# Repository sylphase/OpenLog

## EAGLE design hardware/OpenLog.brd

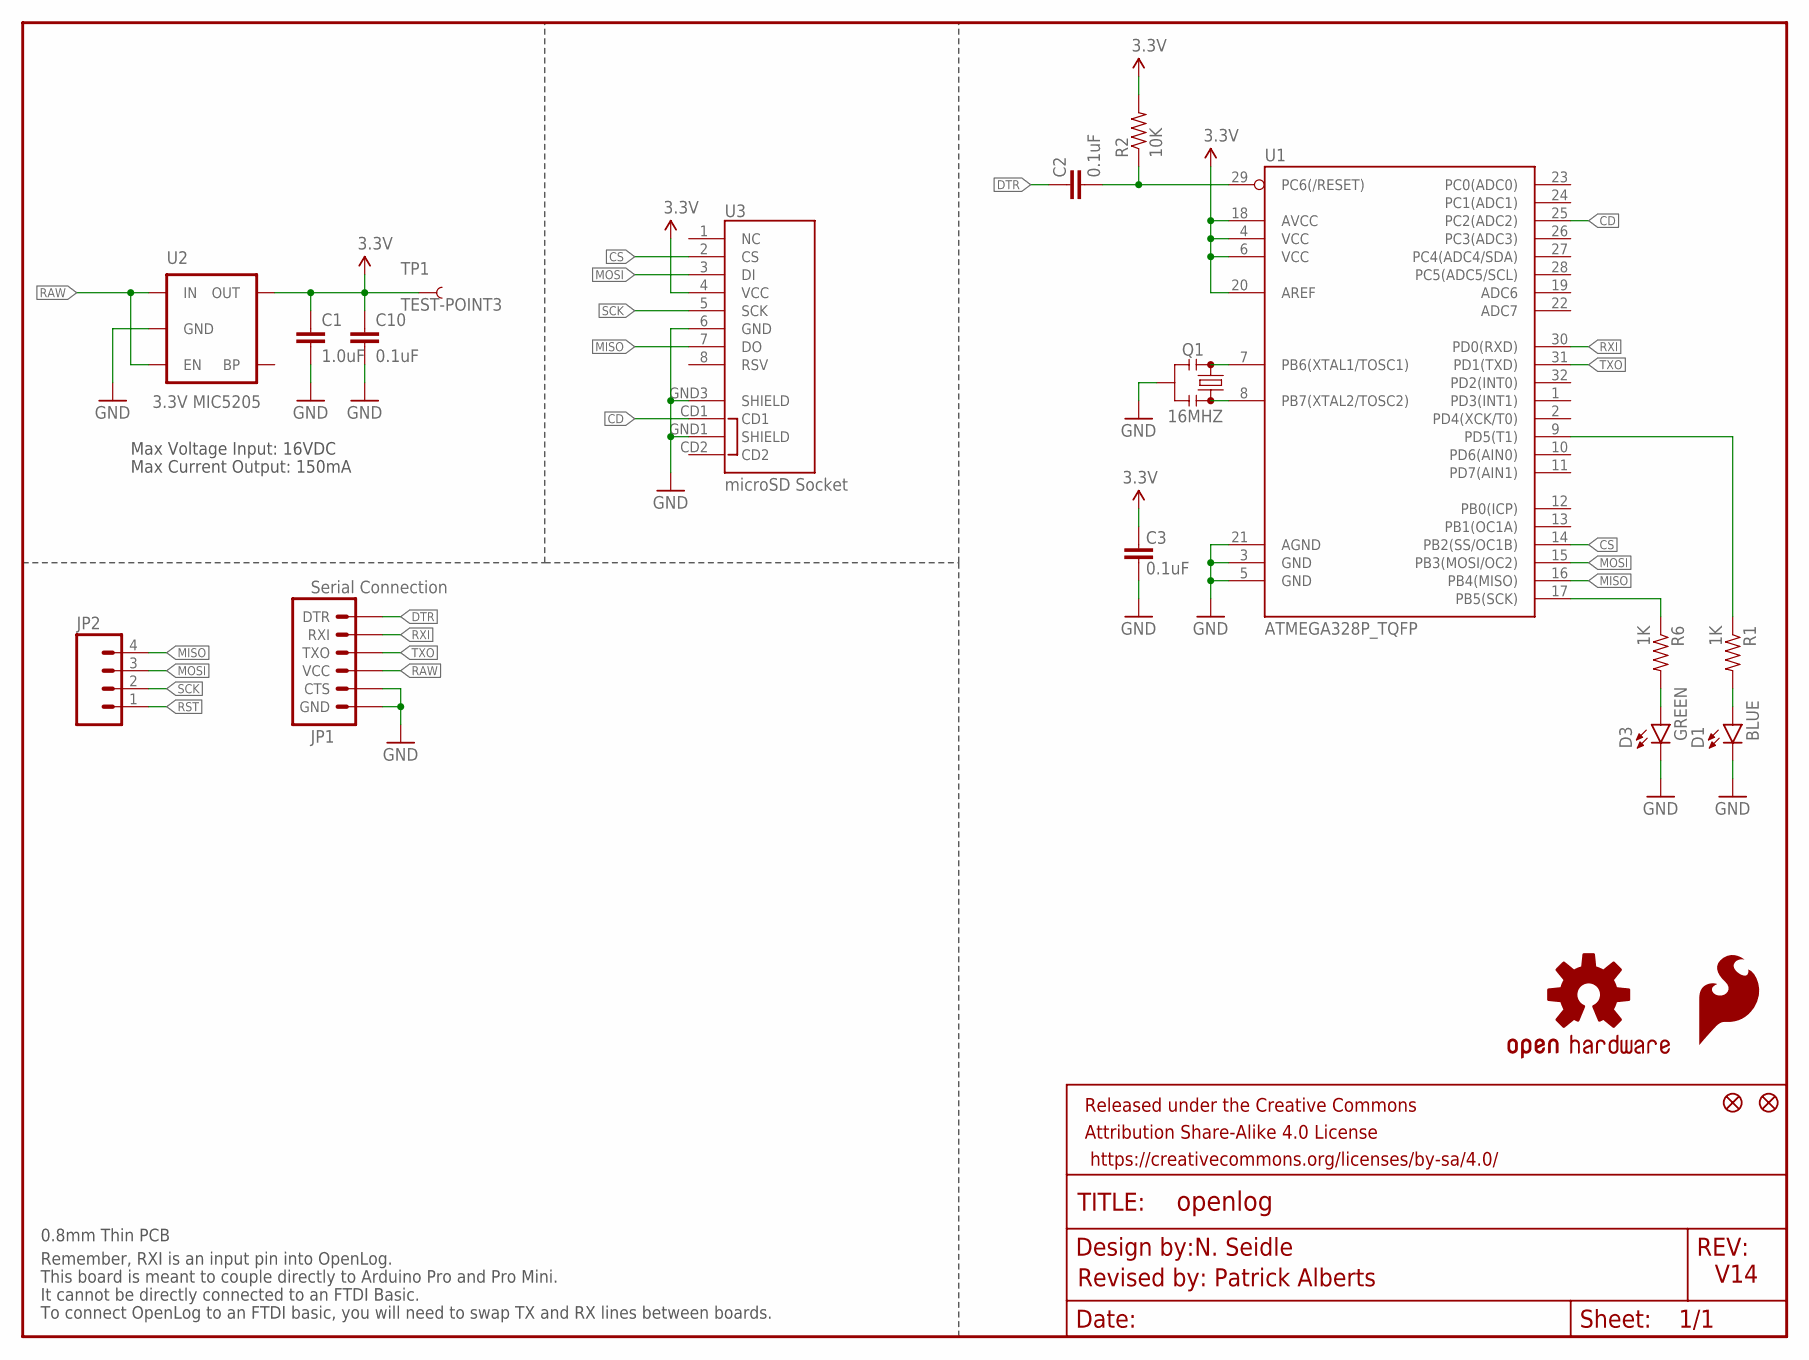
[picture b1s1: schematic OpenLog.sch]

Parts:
C1: 1.0uF; 0603-CAP
C2, C3, C10: 0.1uF; 0603-CAP
D1: BLUE; LED-0603
D3: GREEN; LED-0603
FID1, FID2: FIDUCIALUFIDUCIAL; MICRO-FIDUCIAL
FRAME1: FRAME-LETTER; CREATIVE_COMMONS
JP1: Serial Connection; 1X06
JP2: M04PTH; 1X04
LOGO1: SFE_LOGO_FLAME.1_INCH; SFE_LOGO_FLAME_.1
LOGO2: OSHW-LOGOS; OSHW-LOGO-S
Q1: 16MHZ; RESONATOR-SMD
R1, R6: 1K; 0603-RES
R2: 10K; 0603-RES
TP1: TEST-POINT3; PAD.03X.03
U1: ATMEGA328P_TQFP; TQFP32-08
U2: 3.3V MIC5205; SOT23-5
U3: microSD Socket; MICROSD_1:1

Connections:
3.3V: C1.1, C3.2, C10.1, R2.2, TP1.P$1, U1.4 (VCC), U1.6 (VCC), U1.18 (AVCC), U1.20 (AREF), U2.5 (OUT), U3.4 (VCC)
CD: U1.25 (PC2(ADC2)), U3.CD1
CS: U1.14 (PB2(SS/OC1B)), U3.2 (CS)
DTR: C2.2, JP1.1 (DTR)
GND: C1.2, C3.1, C10.2, D1.C, D3.C, JP1.5 (CTS), JP1.6 (GND), Q1.2, U1.3 (GND), U1.5 (GND), U1.21 (AGND), U2.2 (GND), U3.6 (GND), U3.GND1 (SHIELD), U3.GND3 (SHIELD)
MISO: JP2.4, U1.16 (PB4(MISO)), U3.7 (DO)
MOSI: JP2.3, U1.15 (PB3(MOSI/OC2)), U3.3 (DI)
unnamed: Q1.1, U1.8 (PB7(XTAL2/TOSC2))
unnamed: Q1.3, U1.7 (PB6(XTAL1/TOSC1))
unnamed: D1.A, R1.2
unnamed: R1.1, U1.9 (PD5(T1))
unnamed: D3.A, R6.2
RAW: JP1.4 (VCC), U2.1 (IN), U2.3 (EN)
RST: C2.1, JP2.1, R2.1, U1.29 (PC6(/RESET))
RXI: JP1.2 (RXI), U1.30 (PD0(RXD))
SCK: JP2.2, R6.1, U1.17 (PB5(SCK)), U3.5 (SCK)
TXO: JP1.3 (TXO), U1.31 (PD1(TXD))

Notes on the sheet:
Max Voltage Input: 16VDC
Max Current Output: 150mA
Remember, RXI is an input pin into OpenLog.
This board is meant to couple directly to Arduino Pro and Pro Mini.
It cannot be directly connected to an FTDI Basic.
To connect OpenLog to an FTDI basic, you will need to swap TX and RX lines between boards.
V14
N. Seidle
Revised by: Patrick Alberts
0.8mm Thin PCB

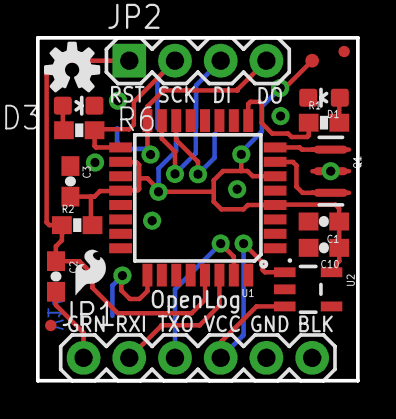
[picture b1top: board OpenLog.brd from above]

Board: 2 copper layers, 17.8 x 19.1 mm, 21 parts (1 on the bottom side), 17 nets.

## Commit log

2015-06-02 Added Test point , removed OSHW logo
2015-06-02 Headers moved on grid.
2015-06-02 Added OSHW logo, fixed trace
2015-06-13 output contents of banner.txt over serial port on startup (if it exists)
2015-06-13 allow adding 2000000 to baud rate in config.txt for even parity and 4000000 for odd parity
2015-06-19 changed banner file to be a list of commands
2015-06-21 oops, this isn't Python!

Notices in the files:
parts and their libraries:
SparkFun-Connectors: Licensing: Creative Commons ShareAlike 4.0 International - https://creativecommons.org/licenses/by-sa/4.0
SparkFun-Aesthetics: Released under the Creative Commons Attribution Share-Alike 4.0 License
SparkFun-Aesthetics: https://creativecommons.org/licenses/by-sa/4.0
